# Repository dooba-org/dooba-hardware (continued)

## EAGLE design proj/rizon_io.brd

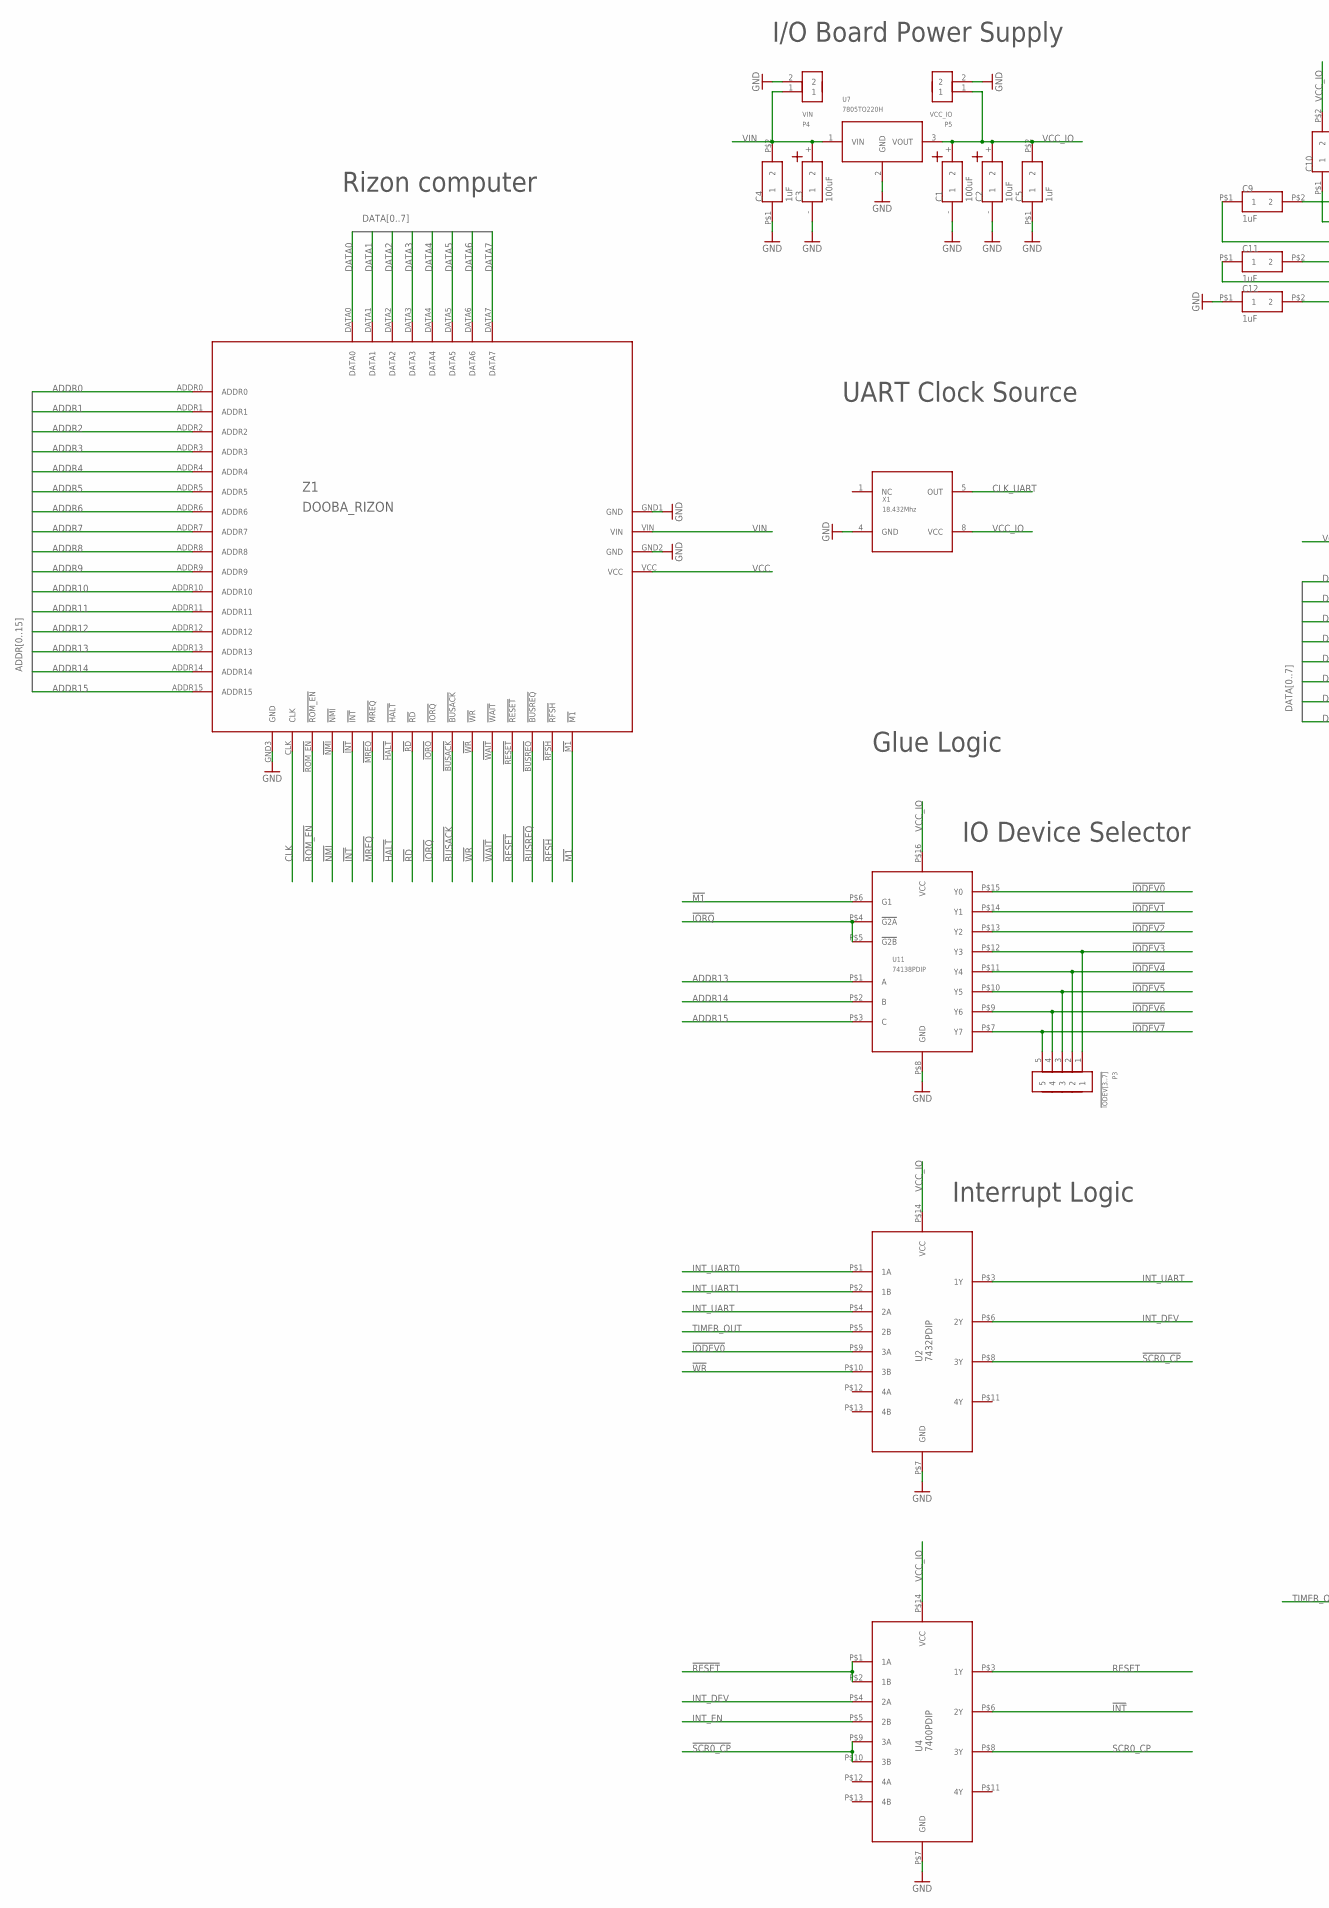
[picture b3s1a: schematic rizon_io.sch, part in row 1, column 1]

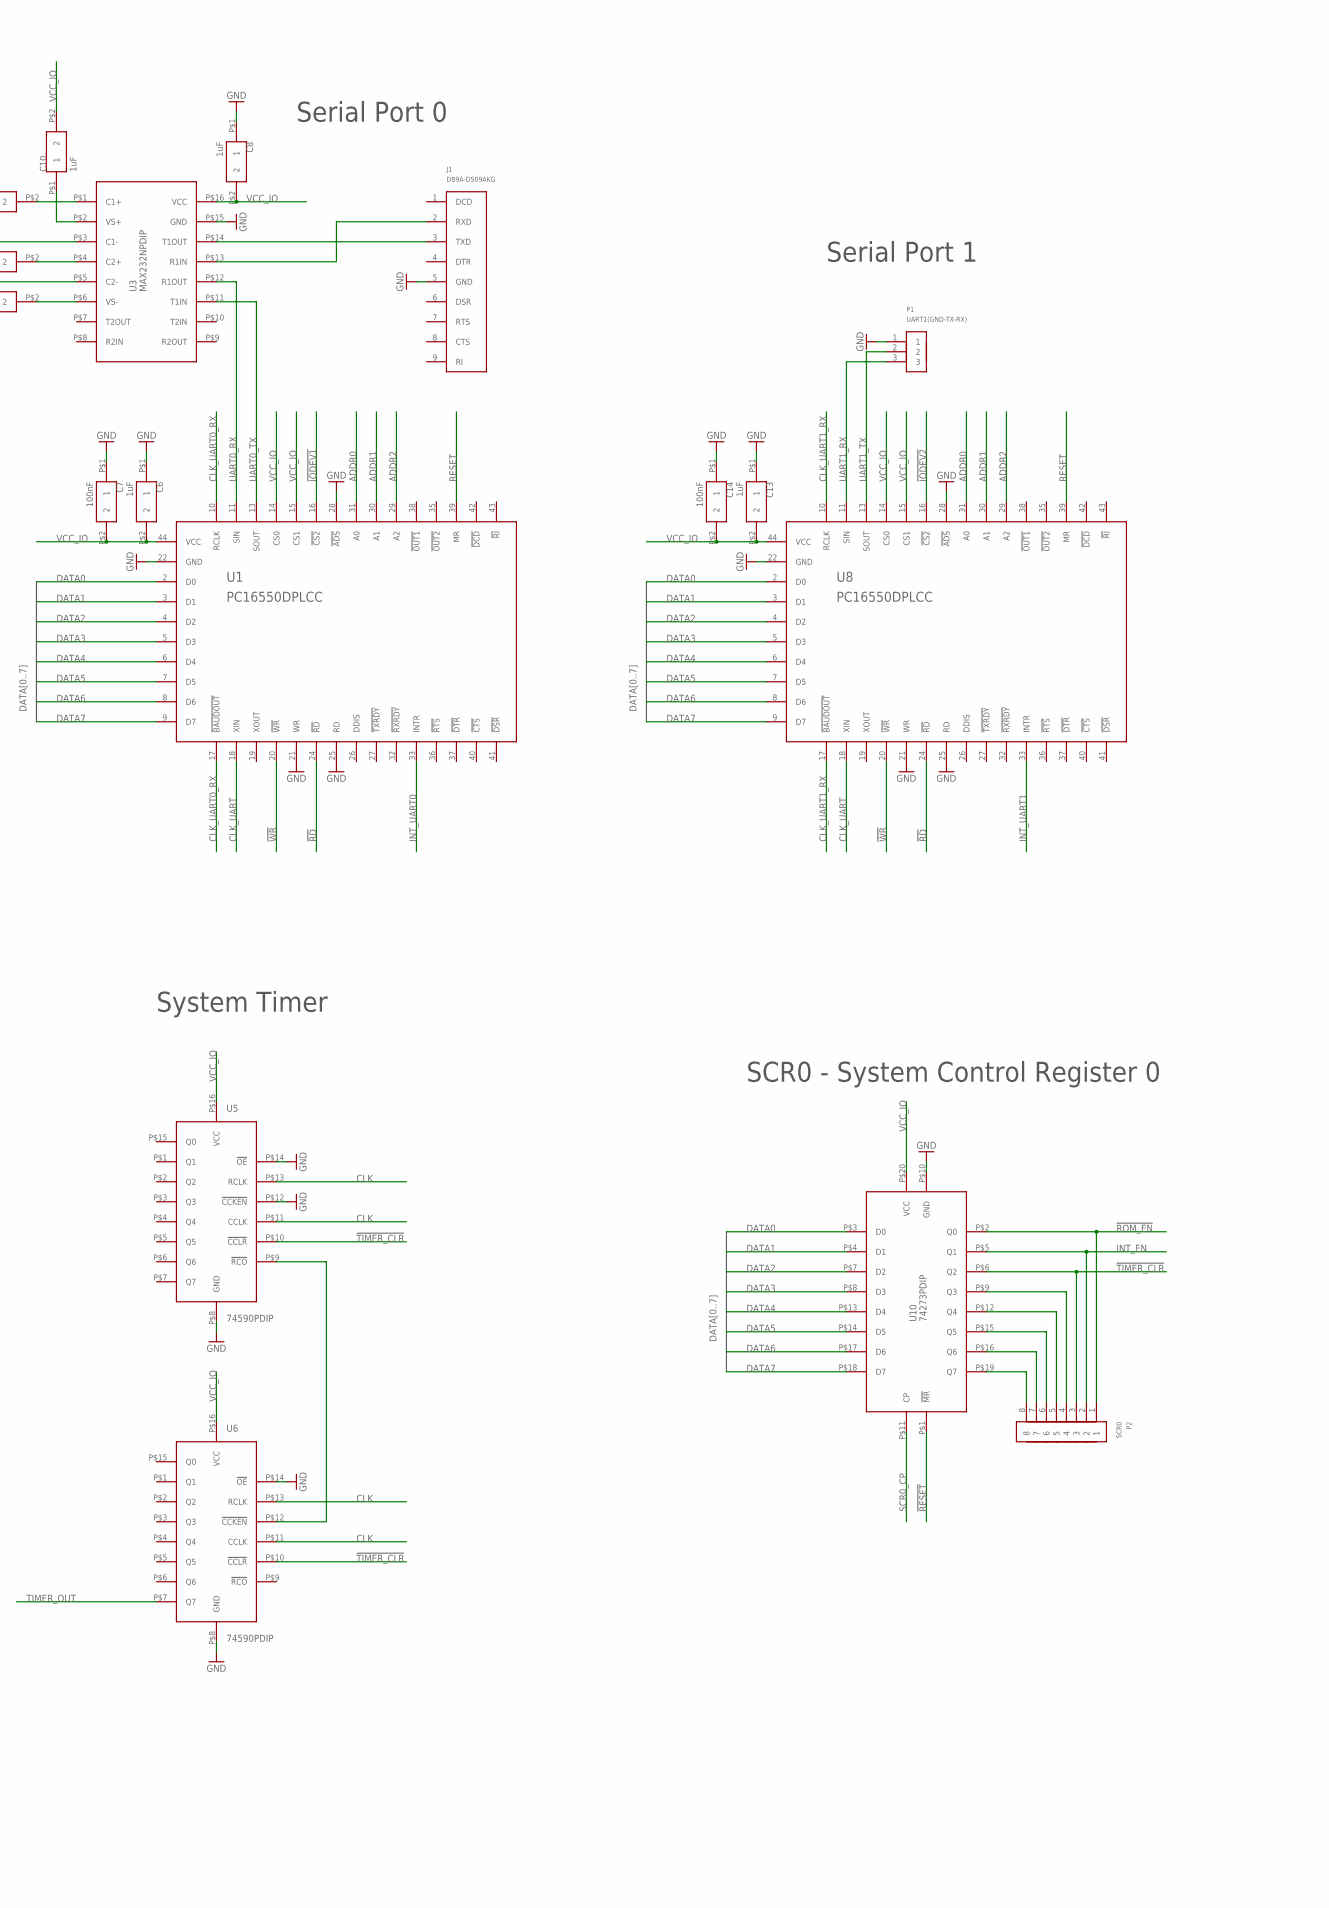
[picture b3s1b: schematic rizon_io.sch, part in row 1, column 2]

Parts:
C1, C3: 100uF; RADCAP_5MM
C2: 10uF; RADCAP_5MM
C4, C5, C6, C8, C9, C10, C11, C12, C13: 1uF; CAP_508
C7, C14: 100nF; CAP_DISC
J1: DB9A-DS09AKG; A-DS09AKG
P1: UART1(GND-TX-RX); PIN_3
P2: SCR0; PIN_8
P3: !IODEV[3..7]; PIN_5
P4: VIN; PIN_2
P5: VCC_IO; PIN_2
U1, U8: PC16550DPLCC; PLCC-S44-SOCKET
U2: 7432PDIP; PDIP14
U3: MAX232NPDIP; PDIP16
U4: 7400PDIP; PDIP14
U5, U6: 74590PDIP; PDIP16
U7: 7805TO220H; TO220H
U10: 74273PDIP; PDIP20
U11: 74138PDIP; PDIP16
X1: 18.432Mhz; OSC127
Z1: DOOBA_RIZON

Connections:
!BUSACK: Z1.!BUSACK
!BUSREQ: Z1.!BUSREQ
!HALT: Z1.!HALT
!INT: U4.P$6 (2Y), Z1.!INT
!IODEV0: U2.P$9 (3A), U11.P$15 (Y0)
!IODEV1: U1.16 (!CS2), U11.P$14 (Y1)
!IODEV2: U8.16 (!CS2), U11.P$13 (Y2)
!IODEV3: P3.1, U11.P$12 (Y3)
!IODEV4: P3.2, U11.P$11 (Y4)
!IODEV5: P3.3, U11.P$10 (Y5)
!IODEV6: P3.4, U11.P$9 (Y6)
!IODEV7: P3.5, U11.P$7 (Y7)
!IORQ: U11.P$4 (!G2A), U11.P$5 (!G2B), Z1.!IORQ
!M1: U11.P$6 (G1), Z1.!M1
!MREQ: Z1.!MREQ
!NMI: Z1.!NMI
!RD: U1.24 (!RD), U8.24 (!RD), Z1.!RD
!RESET: U4.P$1 (1A), U4.P$2 (1B), U10.P$1 (!MR), Z1.!RESET
!RFSH: Z1.!RFSH
!ROM_EN: P2.1, U10.P$2 (Q0), Z1.!ROM_EN
!SCR0_CP: U2.P$8 (3Y), U4.P$9 (3A), U4.P$10 (3B)
!TIMER_CLR: P2.3, U5.P$10 (!CCLR), U6.P$10 (!CCLR), U10.P$6 (Q2)
!WAIT: Z1.!WAIT
!WR: U1.20 (!WR), U2.P$10 (3B), U8.20 (!WR), Z1.!WR
ADDR0: U1.31 (A0), U8.31 (A0), Z1.ADDR0
ADDR1: U1.30 (A1), U8.30 (A1), Z1.ADDR1
ADDR2: U1.29 (A2), U8.29 (A2), Z1.ADDR2
ADDR3: Z1.ADDR3
ADDR4: Z1.ADDR4
ADDR5: Z1.ADDR5
ADDR6: Z1.ADDR6
ADDR7: Z1.ADDR7
ADDR8: Z1.ADDR8
ADDR9: Z1.ADDR9
ADDR10: Z1.ADDR10
ADDR11: Z1.ADDR11
ADDR12: Z1.ADDR12
ADDR13: U11.P$1 (A), Z1.ADDR13
ADDR14: U11.P$2 (B), Z1.ADDR14
ADDR15: U11.P$3 (C), Z1.ADDR15
CLK: U5.P$11 (CCLK), U5.P$13 (RCLK), U6.P$11 (CCLK), U6.P$13 (RCLK), Z1.CLK
CLK_UART: U1.18 (XIN), U8.18 (XIN), X1.5 (OUT)
CLK_UART0_RX: U1.10 (RCLK), U1.17 (!BAUDOUT)
CLK_UART1_RX: U8.10 (RCLK), U8.17 (!BAUDOUT)
DATA0: U1.2 (D0), U8.2 (D0), U10.P$3 (D0), Z1.DATA0
DATA1: U1.3 (D1), U8.3 (D1), U10.P$4 (D1), Z1.DATA1
DATA2: U1.4 (D2), U8.4 (D2), U10.P$7 (D2), Z1.DATA2
DATA3: U1.5 (D3), U8.5 (D3), U10.P$8 (D3), Z1.DATA3
DATA4: U1.6 (D4), U8.6 (D4), U10.P$13 (D4), Z1.DATA4
DATA5: U1.7 (D5), U8.7 (D5), U10.P$14 (D5), Z1.DATA5
DATA6: U1.8 (D6), U8.8 (D6), U10.P$17 (D6), Z1.DATA6
DATA7: U1.9 (D7), U8.9 (D7), U10.P$18 (D7), Z1.DATA7
GND: C1.- (1), C2.- (1), C3.- (1), C4.P$1 (1), C5.P$1 (1), C6.P$1 (1), C7.P$1 (1), C8.P$1 (1), C12.P$1 (1), C13.P$1 (1), C14.P$1 (1), J1.5 (GND), P1.1, P4.2, P5.2, U1.21 (WR), U1.22 (GND), U1.25 (RD), U1.28 (!ADS), U2.P$7 (GND), U3.P$15 (GND), U4.P$7 (GND), U5.P$8 (GND), U5.P$12 (!CCKEN), U5.P$14 (!OE), U6.P$8 (GND), U6.P$14 (!OE), U7.2 (GND), U8.21 (WR), U8.22 (GND), U8.25 (RD), U8.28 (!ADS), U10.P$10 (GND), U11.P$8 (GND), X1.4 (GND), Z1.GND1 (GND), Z1.GND2 (GND), Z1.GND3 (GND)
INT_DEV: U2.P$6 (2Y), U4.P$4 (2A)
INT_EN: P2.2, U4.P$5 (2B), U10.P$5 (Q1)
INT_UART: U2.P$3 (1Y), U2.P$4 (2A)
INT_UART0: U1.33 (INTR), U2.P$1 (1A)
INT_UART1: U2.P$2 (1B), U8.33 (INTR)
unnamed: U5.P$9 (!RCO), U6.P$12 (!CCKEN)
unnamed: C11.P$2 (2), U3.P$4 (C2+)
unnamed: C11.P$1 (1), U3.P$5 (C2-)
unnamed: C9.P$1 (1), U3.P$3 (C1-)
unnamed: C9.P$2 (2), U3.P$1 (C1+)
unnamed: C10.P$1 (1), U3.P$2 (VS+)
unnamed: C12.P$2 (2), U3.P$6 (VS-)
unnamed: J1.3 (TXD), U3.P$14 (T1OUT)
unnamed: J1.2 (RXD), U3.P$13 (R1IN)
unnamed: P2.8, U10.P$19 (Q7)
unnamed: P2.7, U10.P$16 (Q6)
unnamed: P2.6, U10.P$15 (Q5)
unnamed: P2.5, U10.P$12 (Q4)
unnamed: P2.4, U10.P$9 (Q3)
RESET: U1.39 (MR), U4.P$3 (1Y), U8.39 (MR)
SCR0_CP: U4.P$8 (3Y), U10.P$11 (CP)
TIMER_OUT: U2.P$5 (2B), U6.P$7 (Q7)
UART0_RX: U1.11 (SIN), U3.P$12 (R1OUT)
UART0_TX: U1.13 (SOUT), U3.P$11 (T1IN)
UART1_RX: P1.3, U8.11 (SIN)
UART1_TX: P1.2, U8.13 (SOUT)
VCC: Z1.VCC
VCC_IO: C1.+ (2), C2.+ (2), C5.P$2 (2), C6.P$2 (2), C7.P$2 (2), C8.P$2 (2), C10.P$2 (2), C13.P$2 (2), C14.P$2 (2), P5.1, U1.14 (CS0), U1.15 (CS1), U1.44 (VCC), U2.P$14 (VCC), U3.P$16 (VCC), U4.P$14 (VCC), U5.P$16 (VCC), U6.P$16 (VCC), U7.3 (VOUT), U8.14 (CS0), U8.15 (CS1), U8.44 (VCC), U10.P$20 (VCC), U11.P$16 (VCC), X1.8 (VCC)
VIN: C3.+ (2), C4.P$2 (2), P4.1, U7.1 (VIN), Z1.VIN

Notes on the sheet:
IO Device Selector
Serial Port 0
UART Clock Source
I/O Board Power Supply
Rizon computer
System Timer
SCR0 - System Control Register 0
Glue Logic
Interrupt Logic
Serial Port 1

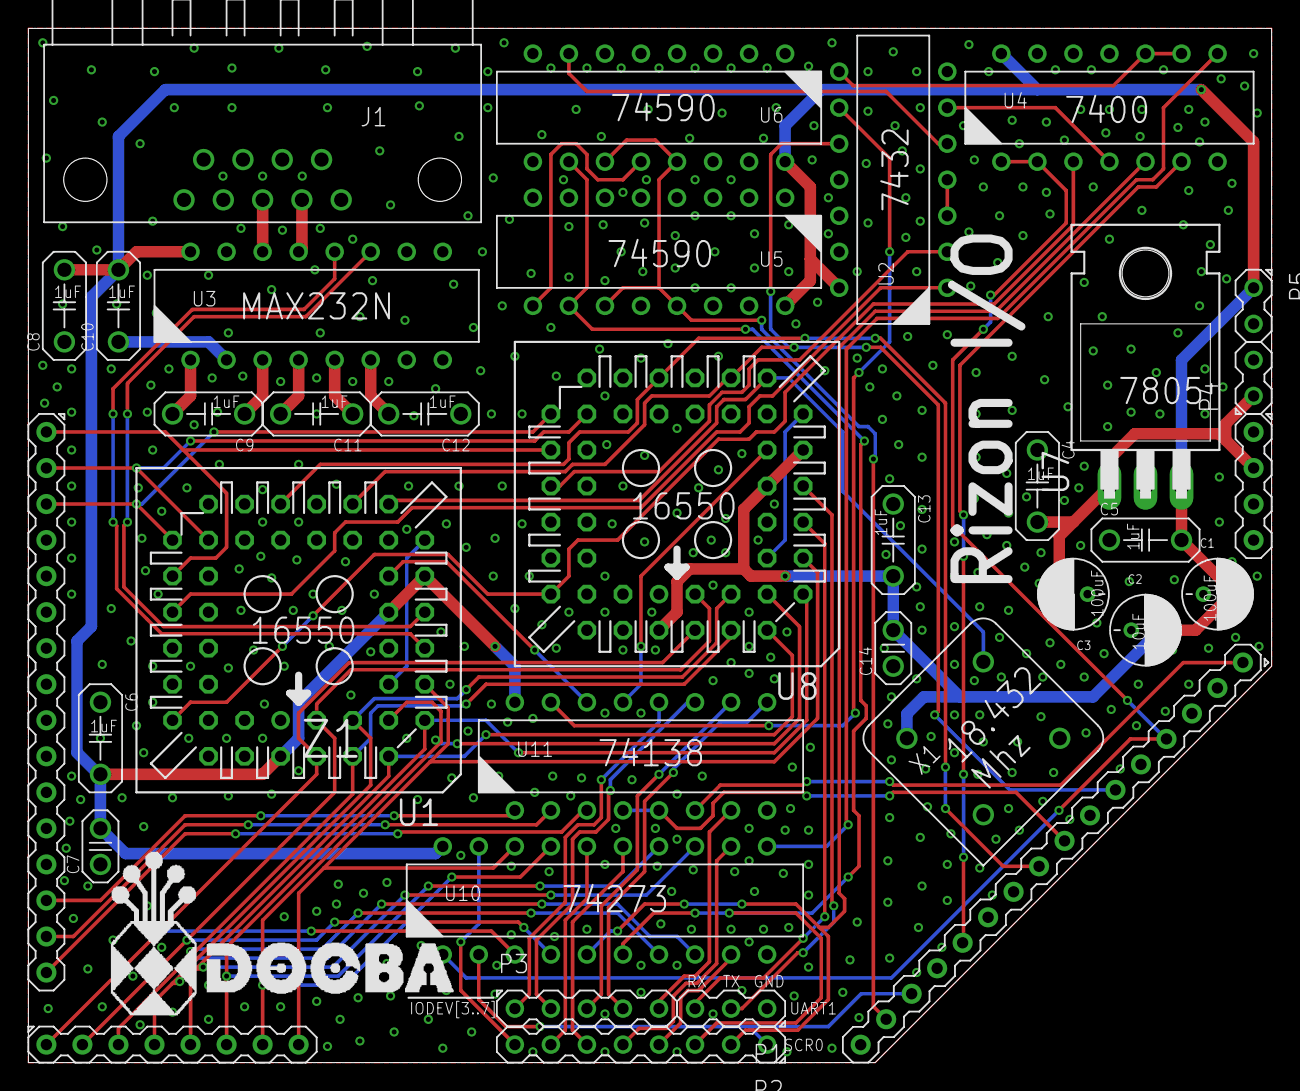
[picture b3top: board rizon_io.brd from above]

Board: 2 copper layers, 87.6 x 72.9 mm, 32 parts (0 on the bottom side), 64 nets.

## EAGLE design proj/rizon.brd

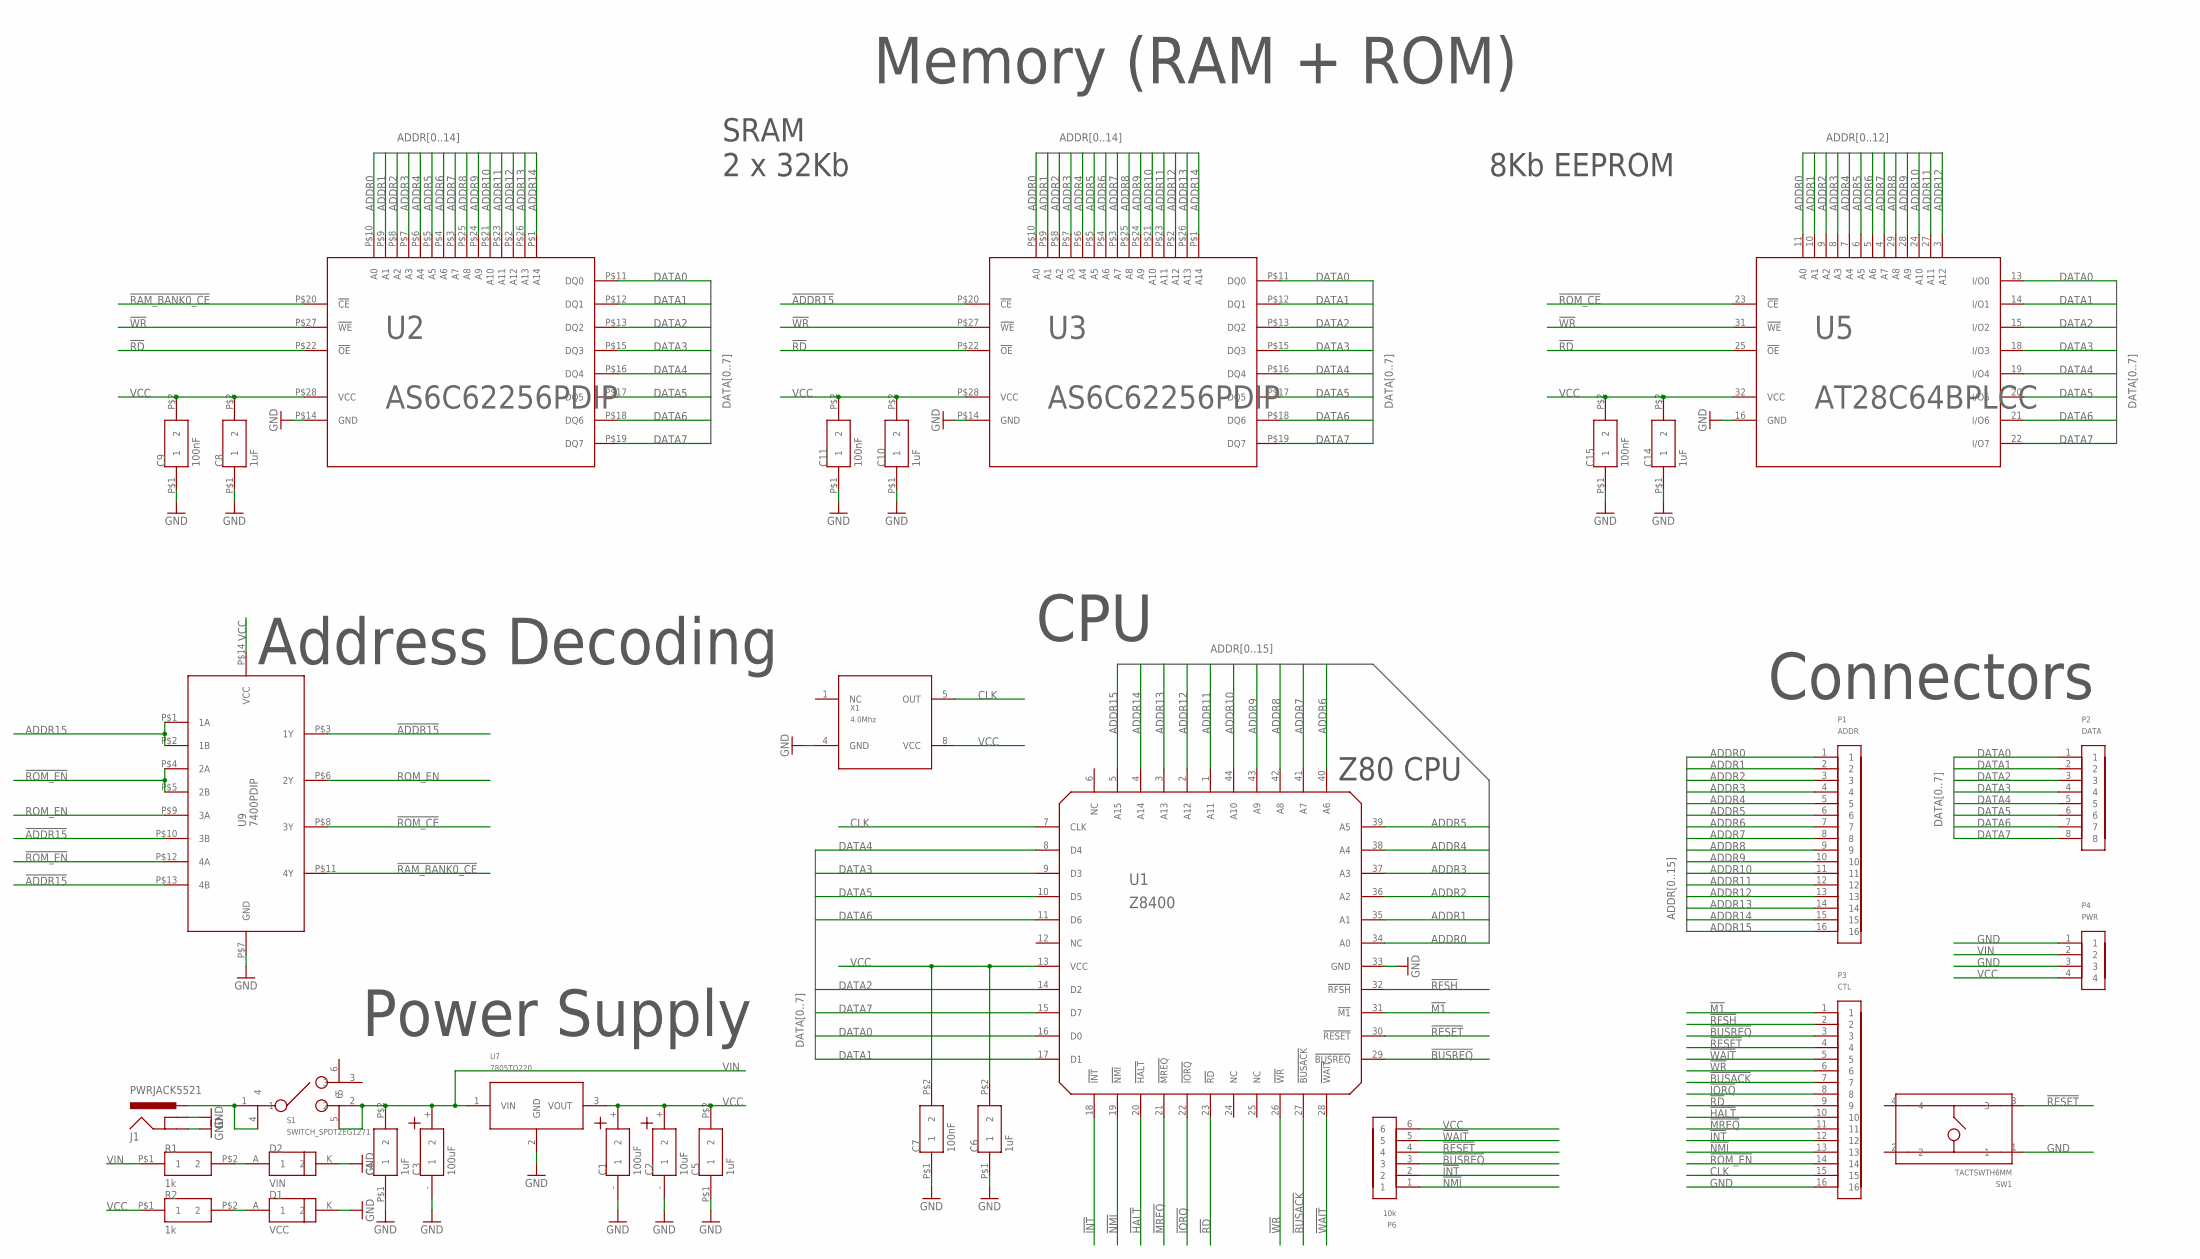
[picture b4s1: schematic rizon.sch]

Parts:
C1, C3: 100uF; RADCAP_5MM
C2: 10uF; RADCAP_5MM
C4, C5, C6, C8, C10, C14: 1uF; CAP_508
C7, C9, C11, C15: 100nF; CAP_DISC
D1: VCC; LED5MM
D2: VIN; LED5MM
J1: PWRJACK5521; PWRJACK_5521
P1: ADDR; PIN_16
P2: DATA; PIN_8
P3: CTL; PIN_16
P4: PWR; PIN_4
P6: 10k; PIN_6
R1, R2: 1k; RES8MM
S1: SWITCH_SPDT2EG1271; EG1271
SW1: TACTSWTH6MM; SWITCH_6MM
U1: Z8400; PLCC-S44-SOCKET
U2, U3: AS6C62256PDIP; PDIP28-600
U5: AT28C64BPLCC; PLCC-S32--SOCKET
U7: 7805TO220; TO220V
U9: 7400PDIP; PDIP14
X1: 4.0Mhz; OSC127

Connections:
!ADDR15: U3.P$20 (!CE), U9.P$3 (1Y), U9.P$10 (3B), U9.P$13 (4B)
!BUSACK: P3.7, U1.27 (!BUSACK)
!BUSREQ: P3.3, P6.3, U1.29 (!BUSREQ)
!HALT: P3.10, U1.20 (!HALT)
!INT: P3.12, P6.2, U1.18 (!INT)
!IORQ: P3.8, U1.22 (!IORQ)
!M1: P3.1, U1.31 (!M1)
!MREQ: P3.11, U1.21 (!MREQ)
!NMI: P3.13, P6.1, U1.19 (!NMI)
!RAM_BANK0_CE: U2.P$20 (!CE), U9.P$11 (4Y)
!RD: P3.9, U1.23 (!RD), U2.P$22 (!OE), U3.P$22 (!OE), U5.25 (!OE)
!RESET: P3.4, P6.4, SW1.3, U1.30 (!RESET)
!RFSH: P3.2, U1.32 (!RFSH)
!ROM_CE: U5.23 (!CE), U9.P$8 (3Y)
!ROM_EN: P3.14, U9.P$4 (2A), U9.P$5 (2B), U9.P$12 (4A)
!WAIT: P3.5, P6.5, U1.28 (!WAIT)
!WR: P3.6, U1.26 (!WR), U2.P$27 (!WE), U3.P$27 (!WE), U5.31 (!WE)
ADDR0: P1.1, U1.34 (A0), U2.P$10 (A0), U3.P$10 (A0), U5.11 (A0)
ADDR1: P1.2, U1.35 (A1), U2.P$9 (A1), U3.P$9 (A1), U5.10 (A1)
ADDR2: P1.3, U1.36 (A2), U2.P$8 (A2), U3.P$8 (A2), U5.9 (A2)
ADDR3: P1.4, U1.37 (A3), U2.P$7 (A3), U3.P$7 (A3), U5.8 (A3)
ADDR4: P1.5, U1.38 (A4), U2.P$6 (A4), U3.P$6 (A4), U5.7 (A4)
ADDR5: P1.6, U1.39 (A5), U2.P$5 (A5), U3.P$5 (A5), U5.6 (A5)
ADDR6: P1.7, U1.40 (A6), U2.P$4 (A6), U3.P$4 (A6), U5.5 (A6)
ADDR7: P1.8, U1.41 (A7), U2.P$3 (A7), U3.P$3 (A7), U5.4 (A7)
ADDR8: P1.9, U1.42 (A8), U2.P$25 (A8), U3.P$25 (A8), U5.29 (A8)
ADDR9: P1.10, U1.43 (A9), U2.P$24 (A9), U3.P$24 (A9), U5.28 (A9)
ADDR10: P1.11, U1.44 (A10), U2.P$21 (A10), U3.P$21 (A10), U5.24 (A10)
ADDR11: P1.12, U1.1 (A11), U2.P$23 (A11), U3.P$23 (A11), U5.27 (A11)
ADDR12: P1.13, U1.2 (A12), U2.P$2 (A12), U3.P$2 (A12), U5.3 (A12)
ADDR13: P1.14, U1.3 (A13), U2.P$26 (A13), U3.P$26 (A13)
ADDR14: P1.15, U1.4 (A14), U2.P$1 (A14), U3.P$1 (A14)
ADDR15: P1.16, U1.5 (A15), U9.P$1 (1A), U9.P$2 (1B)
CLK: P3.15, U1.7 (CLK), X1.5 (OUT)
DATA0: P2.1, U1.16 (D0), U2.P$11 (DQ0), U3.P$11 (DQ0), U5.13 (I/O0)
DATA1: P2.2, U1.17 (D1), U2.P$12 (DQ1), U3.P$12 (DQ1), U5.14 (I/O1)
DATA2: P2.3, U1.14 (D2), U2.P$13 (DQ2), U3.P$13 (DQ2), U5.15 (I/O2)
DATA3: P2.4, U1.9 (D3), U2.P$15 (DQ3), U3.P$15 (DQ3), U5.18 (I/O3)
DATA4: P2.5, U1.8 (D4), U2.P$16 (DQ4), U3.P$16 (DQ4), U5.19 (I/O4)
DATA5: P2.6, U1.10 (D5), U2.P$17 (DQ5), U3.P$17 (DQ5), U5.20 (I/O5)
DATA6: P2.7, U1.11 (D6), U2.P$18 (DQ6), U3.P$18 (DQ6), U5.21 (I/O6)
DATA7: P2.8, U1.15 (D7), U2.P$19 (DQ7), U3.P$19 (DQ7), U5.22 (I/O7)
GND: C1.- (1), C2.- (1), C3.- (1), C4.P$1 (1), C5.P$1 (1), C6.P$1 (1), C7.P$1 (1), C8.P$1 (1), C9.P$1 (1), C10.P$1 (1), C11.P$1 (1), C14.P$1 (1), C15.P$1 (1), D1.K (2), D2.K (2), J1.GND, J1.GNDBREAK, P3.16, P4.1, P4.3, SW1.1, U1.33 (GND), U2.P$14 (GND), U3.P$14 (GND), U5.16 (GND), U7.2 (GND), U9.P$7 (GND), X1.4 (GND)
unnamed: D2.A (1), R1.P$2 (2)
unnamed: D1.A (1), R2.P$2 (2)
unnamed: J1.PWR, S1.1, S1.4
ROM_EN: U9.P$6 (2Y), U9.P$9 (3A)
VCC: C1.+ (2), C2.+ (2), C5.P$2 (2), C6.P$2 (2), C7.P$2 (2), C8.P$2 (2), C9.P$2 (2), C10.P$2 (2), C11.P$2 (2), C14.P$2 (2), C15.P$2 (2), P4.4, P6.6, R2.P$1 (1), U1.13 (VCC), U2.P$28 (VCC), U3.P$28 (VCC), U5.32 (VCC), U7.3 (VOUT), U9.P$14 (VCC), X1.8 (VCC)
VIN: C3.+ (2), C4.P$2 (2), P4.2, R1.P$1 (1), S1.2, S1.5, U7.1 (VIN)

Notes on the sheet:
SRAM 2 x 32Kb
8Kb EEPROM
Z80 CPU
Address Decoding
Memory (RAM + ROM)
Connectors
Power Supply
CPU

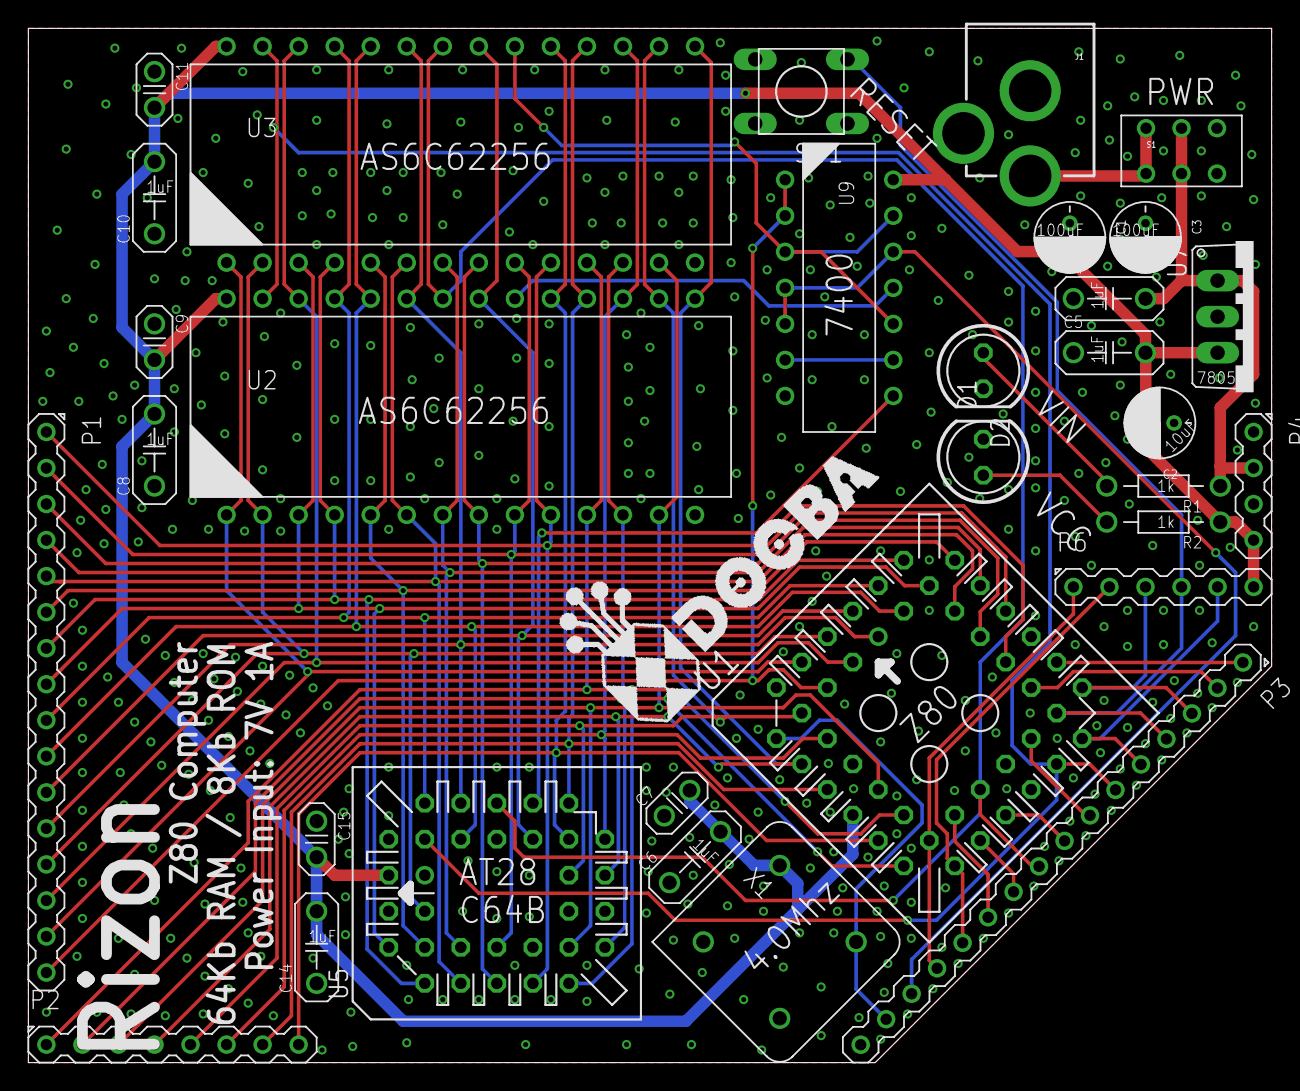
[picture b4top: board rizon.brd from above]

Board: 2 copper layers, 87.6 x 72.9 mm, 32 parts (0 on the bottom side), 49 nets.

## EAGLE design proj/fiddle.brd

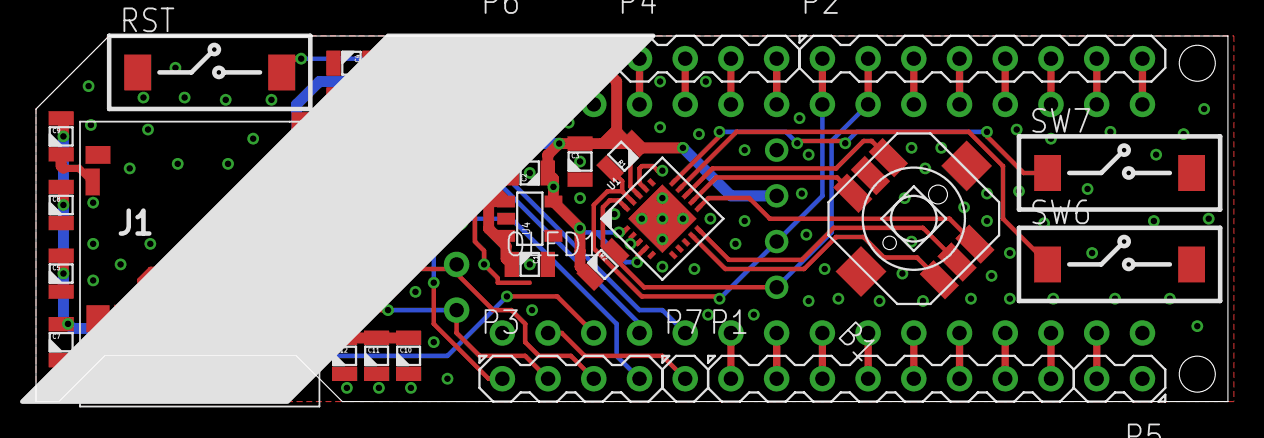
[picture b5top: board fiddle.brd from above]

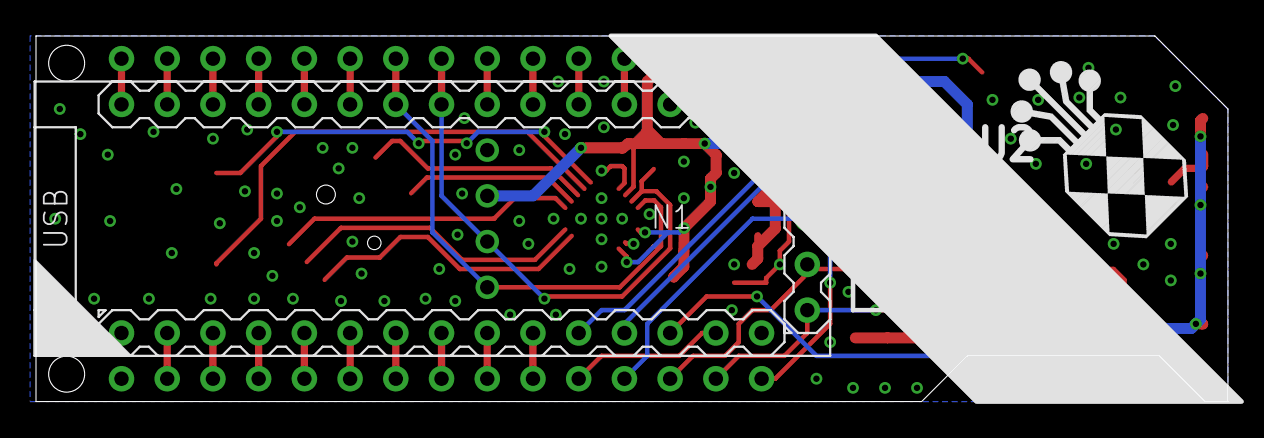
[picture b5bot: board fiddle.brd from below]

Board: 2 copper layers, 66.2 x 20.3 mm, 31 parts (2 on the bottom side), 41 nets.

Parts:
B1: TACTSW_5WAYSMD-7X7; TACTSW-5WAY-7X7
C1, C2: 1uF; 0805
C3, C6, C7: 100nF; 0805
C4, C5, C8, C9, C10, C11, C12: 10uF; 0805
J1: DM3D-SFDM; DM3D-SF
N1: DOOBA_IONODE
OLED1: I2C-OLED-0.91
P1, P2: PIN_8
P3, P4: PIN_4
P5: PIN_2
P6: PIN_3
P7: PIN_1
R1, R2: 10k; 0805
RST: TACTSW_2MICRO3X6; TACTSW_MICRO3X6
SW6, SW7: TACTSW_2MICRO3X6; TACTSW_MICRO3X6
U1: MCP23008QFN; 20-VQFN
U2: WRL-13678WRL-13678-QUIET; WRL-13678-QUIET
U4: 3.3V 600mA; SOT23-5

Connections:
3.3V: C2.2, C3.1, C4.1, C5.1, C6.1, C7.1, C8.1, C9.1, C10.1, C11.1, C12.1, J1.VDD, OLED1.VCC, P6.3, R1.2, R2.2, U1.1, U1.4, U1.18, U2.4, U2.8, U4.5
GND: B1.5, B1.GND1, B1.GND2, C1.1, C2.1, C3.2, C4.2, C5.2, C6.2, C7.2, C8.2, C9.2, C10.2, C11.2, C12.2, J1.GND1, J1.GND2, J1.GND3, J1.GND4, J1.VSS, N1.1, N1.15, N1.35, OLED1.GND, P5.1, P6.1, RST.1, SW6.2, SW7.2, U1.2, U1.3, U1.17, U1.PAD, U2.1, U4.2
I2C_SCL: N1.23, OLED1.SCL, P2.1, R1.1, U1.19
I2C_SDA: N1.24, OLED1.SDA, P2.2, R2.1, U1.20
MICROSD_CS: J1.DAT3/CS, N1.13
unnamed: B1.1, U1.9
unnamed: B1.2, U1.10
unnamed: B1.3, U1.11
unnamed: B1.6, U1.13
unnamed: B1.4, U1.12
unnamed: SW6.1, U1.14
unnamed: SW7.1, U1.15
unnamed: N1.34, P3.1, RST.2
unnamed: N1.30, P2.8
unnamed: N1.29, P2.7
unnamed: N1.28, P2.6
unnamed: N1.27, P2.5
unnamed: N1.26, P2.4
unnamed: N1.25, P2.3
unnamed: N1.3, P1.8
unnamed: N1.4, P1.7
unnamed: N1.5, P1.6
unnamed: N1.6, P1.5
unnamed: N1.7, P1.4
unnamed: N1.8, P1.3
unnamed: N1.9, P1.2
unnamed: N1.10, P1.1
unnamed: N1.22, P4.4
unnamed: N1.21, P4.3
unnamed: N1.20, P4.2
unnamed: N1.19, P4.1
unnamed: N1.14, P7.1
SPI_MISO: J1.DAT0/DO, N1.32, P3.3
SPI_MOSI: J1.CMD/DI, N1.31, P3.2
SPI_SCK: J1.CLK/SCK, N1.33, P3.4
VIN: C1.2, N1.16, P6.2, U4.1, U4.3
VUSB: N1.2, P5.2
WIFI_FLASH: N1.11, U2.5
WIFI_RST: N1.12, U2.6
WIFI_RX: N1.17, U2.2
WIFI_TX: N1.18, U2.7

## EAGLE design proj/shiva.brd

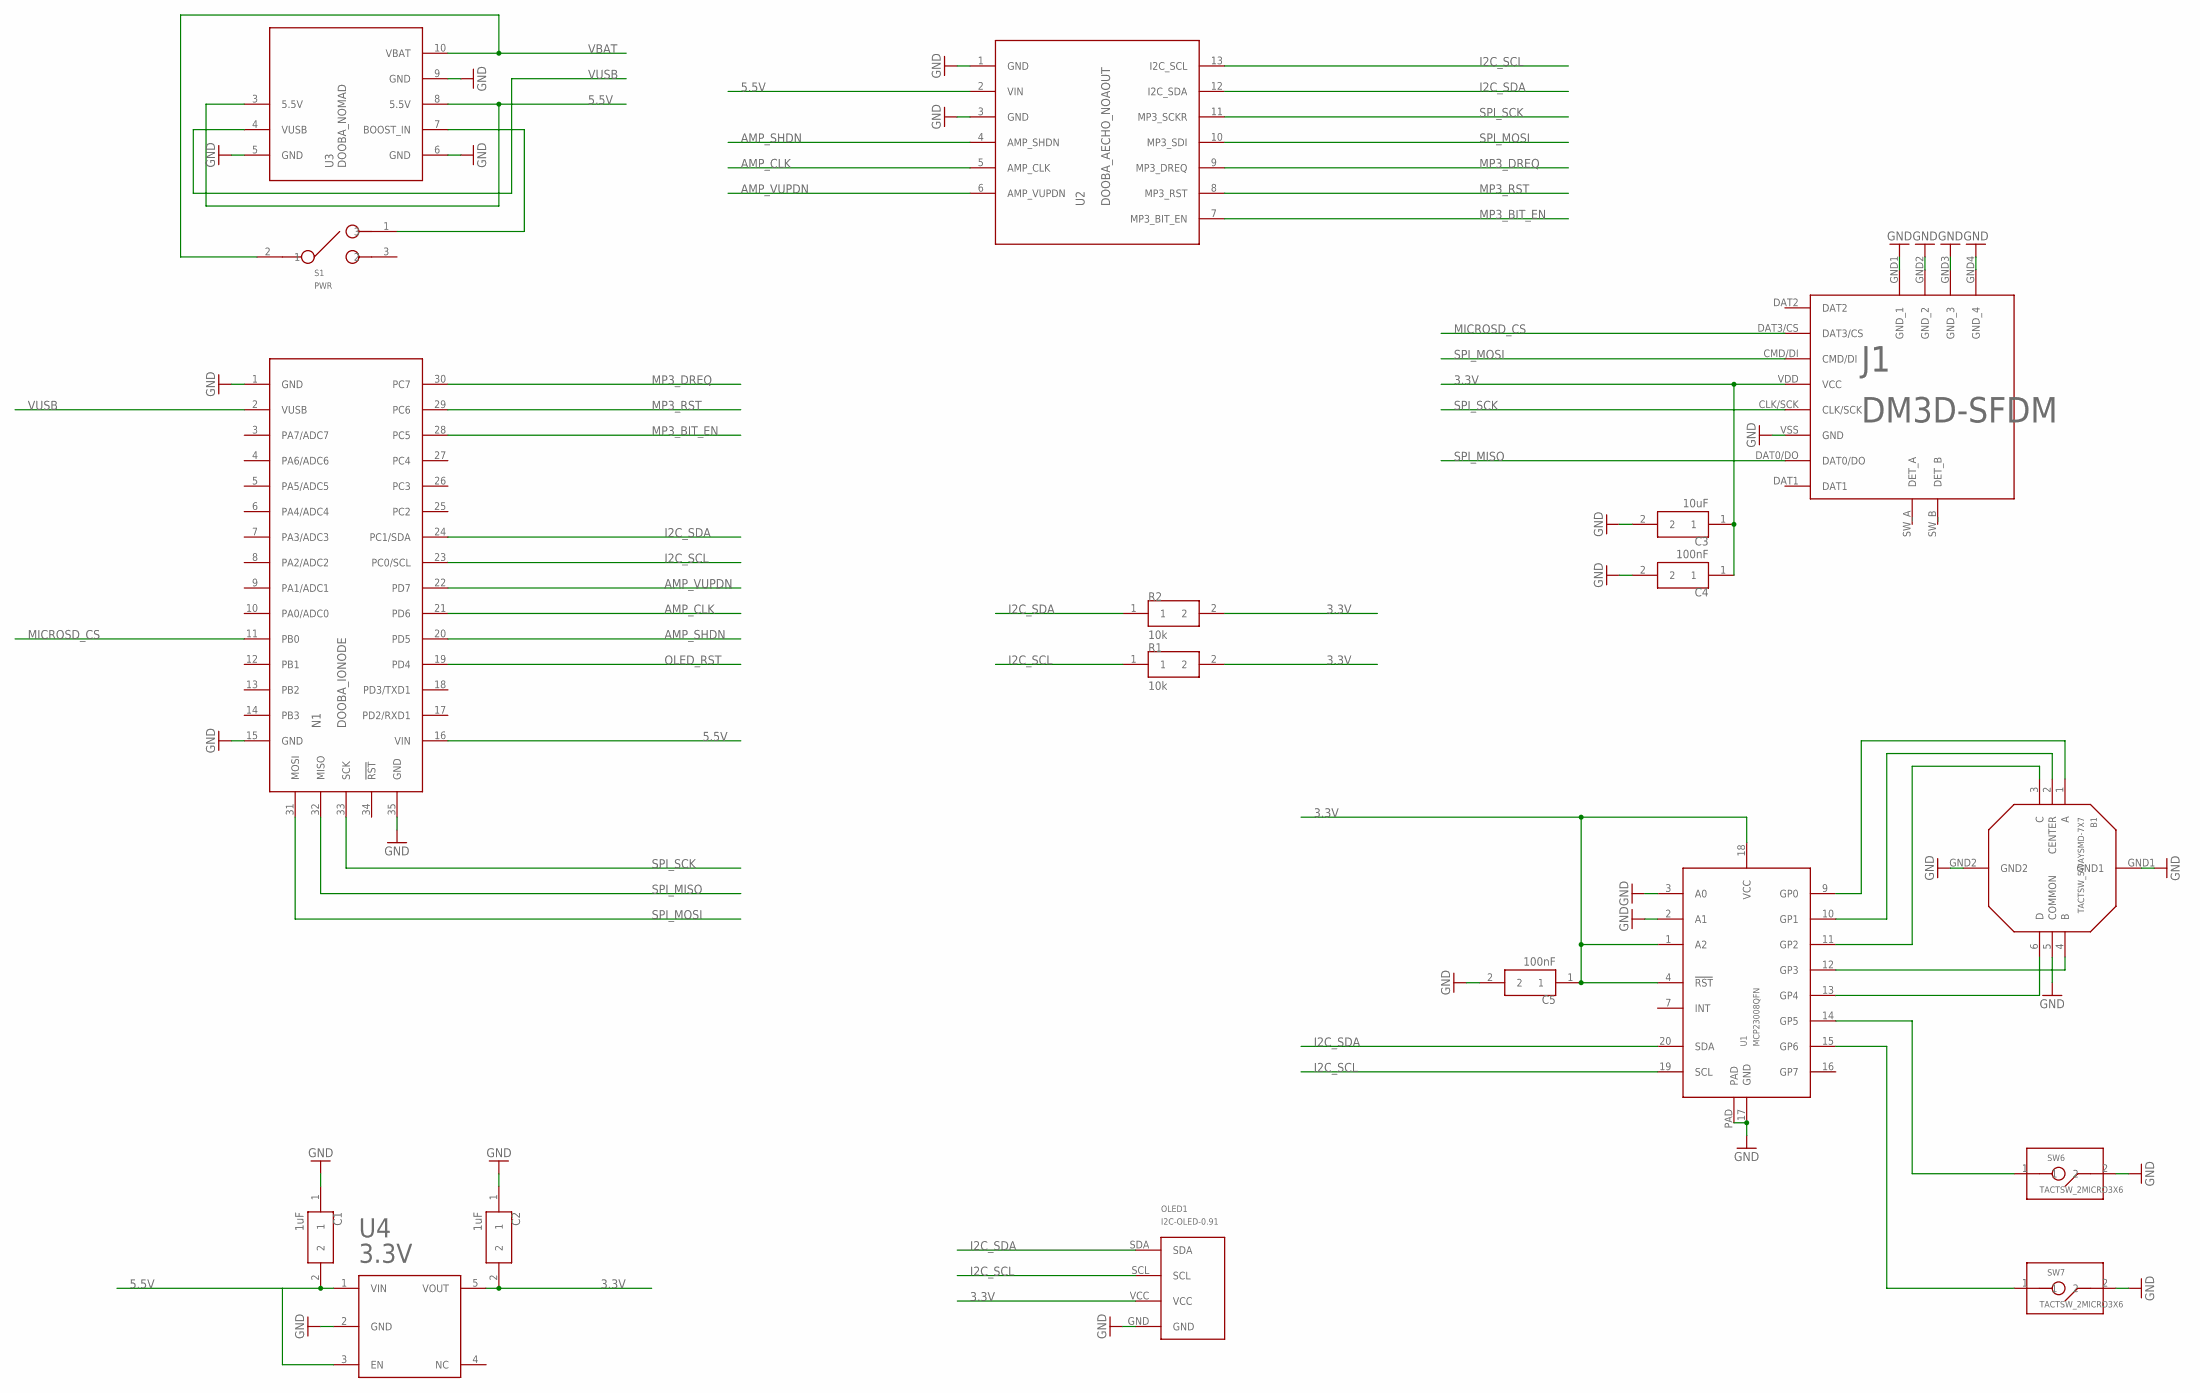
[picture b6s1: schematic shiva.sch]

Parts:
B1: TACTSW_5WAYSMD-7X7; TACTSW-5WAY-7X7
C1, C2: 1uF; 0805
C3: 10uF; 0805
C4, C5: 100nF; 0805
J1: DM3D-SFDM; DM3D-SF
N1: DOOBA_IONODE
OLED1: I2C-OLED-0.91
R1, R2: 10k; 0805
S1: PWR; JS102011
SW6, SW7: TACTSW_2MICRO3X6; TACTSW_MICRO3X6
U1: MCP23008QFN; 20-VQFN
U2: DOOBA_AECHO_NOAOUT
U3: DOOBA_NOMAD
U4: 3.3V; SOT23-5

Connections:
3.3V: C2.2, C3.1, C4.1, C5.1, J1.VDD (VCC), OLED1.VCC, R1.2, R2.2, U1.1 (A2), U1.4 (!RST), U1.18 (VCC), U4.5 (VOUT)
5.5V: C1.2, N1.16 (VIN), U2.2 (VIN), U3.3 (5.5V), U3.8 (5.5V), U4.1 (VIN), U4.3 (EN)
AMP_CLK: N1.21 (PD6), U2.5 (AMP_CLK)
AMP_SHDN: N1.20 (PD5), U2.4 (AMP_SHDN)
AMP_VUPDN: N1.22 (PD7), U2.6 (AMP_VUPDN)
GND: B1.5 (COMMON), B1.GND1, B1.GND2, C1.1, C2.1, C3.2, C4.2, C5.2, J1.GND1 (GND_1), J1.GND2 (GND_2), J1.GND3 (GND_3), J1.GND4 (GND_4), J1.VSS (GND), N1.1 (GND), N1.15 (GND), N1.35 (GND), OLED1.GND, SW6.2, SW7.2, U1.2 (A1), U1.3 (A0), U1.17 (GND), U1.PAD, U2.1 (GND), U2.3 (GND), U3.5 (GND), U3.6 (GND), U3.9 (GND), U4.2 (GND)
I2C_SCL: N1.23 (PC0/SCL), OLED1.SCL, R1.1, U1.19 (SCL), U2.13 (I2C_SCL)
I2C_SDA: N1.24 (PC1/SDA), OLED1.SDA, R2.1, U1.20 (SDA), U2.12 (I2C_SDA)
MICROSD_CS: J1.DAT3/CS, N1.11 (PB0)
MP3_BIT_EN: N1.28 (PC5), U2.7 (MP3_BIT_EN)
MP3_DREQ: N1.30 (PC7), U2.9 (MP3_DREQ)
MP3_RST: N1.29 (PC6), U2.8 (MP3_RST)
unnamed: B1.1 (A), U1.9 (GP0)
unnamed: B1.2 (CENTER), U1.10 (GP1)
unnamed: B1.3 (C), U1.11 (GP2)
unnamed: B1.6 (D), U1.13 (GP4)
unnamed: B1.4 (B), U1.12 (GP3)
unnamed: SW6.1, U1.14 (GP5)
unnamed: SW7.1, U1.15 (GP6)
unnamed: S1.1 (3), U3.7 (BOOST_IN)
OLED_RST: N1.19 (PD4)
SPI_MISO: J1.DAT0/DO, N1.32 (MISO)
SPI_MOSI: J1.CMD/DI, N1.31 (MOSI), U2.10 (MP3_SDI)
SPI_SCK: J1.CLK/SCK, N1.33 (SCK), U2.11 (MP3_SCKR)
VBAT: S1.2 (1), U3.10 (VBAT)
VUSB: N1.2 (VUSB), U3.4 (VUSB)
